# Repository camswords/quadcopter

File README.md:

The ThoughtWorks Sydney Quadcopter
==========

The ThoughtWorks Sydney Quadcopter is a quadcopter that is being built by the ThoughtWorks Sydney Community. 

To find out parts we have used, lessons we have learnt check out http://www.camswords.com/blog. To see photos of the quadcopter as it is built check out http://www.pinterest.com/camswords/the-thoughtworks-sydney-maker-day.

#### To disable Read Out Protection on new devices

1. Download the ST Link utility tool http://www.st.com/web/en/catalog/tools/PF258168

2. Install it on windows

3. Connect your ST Link USB device to your computer, and to your mini-m4

4. Try to connect, it will barf about not having permission. Set the Read Out Protection (under Option Bytes) to Level 0, no protection. 

5. Note that setting it to 2 will brick your mini-m4.

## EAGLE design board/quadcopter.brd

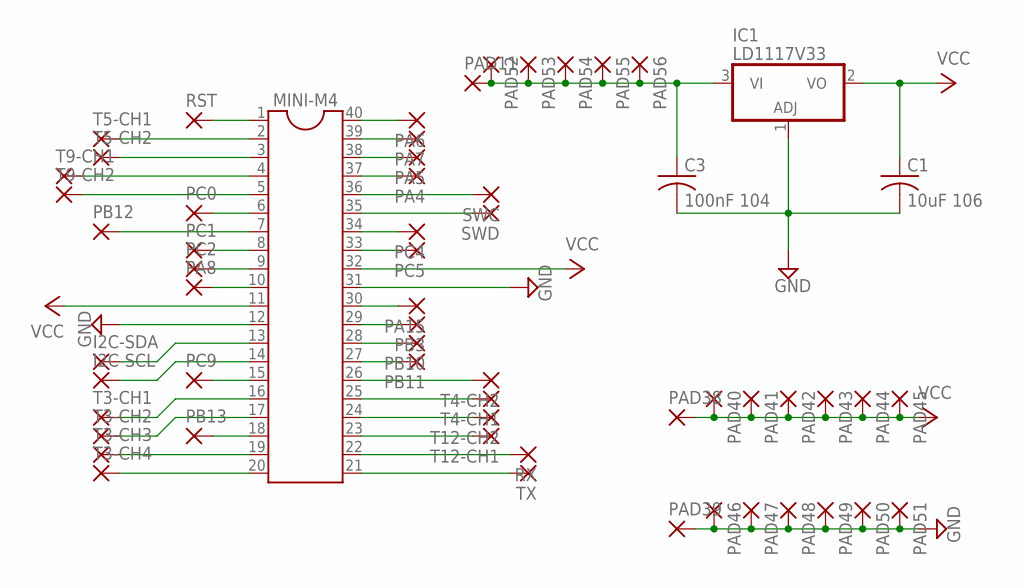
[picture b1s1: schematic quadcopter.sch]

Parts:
C1: 10uF 106; C025-040X050
C3: 100nF 104; C025-040X050
I2C-SCL, I2C-SDA: 1,6/0,8
IC1: LD1117V33; TO220H
MINI-M4: DIL40
PA4, PA5, PA6, PA7, PA8, PA15: 1,6/0,8
PAD11, PAD38, PAD39, PAD40, PAD41, PAD42, PAD43, PAD44, PAD45, PAD46, PAD47, PAD48, PAD49, PAD50, PAD51, PAD52, PAD53, PAD54, PAD55, PAD56: 1,6/0,8
PB3, PB10, PB11, PB12, PB13: 1,6/0,8
PC0, PC1, PC2, PC4, PC5, PC9: 1,6/0,8
RST: 1,6/0,8
RX: 1,6/0,8
SWC: 1,6/0,8
SWD: 1,6/0,8
T3-CH1, T3-CH2, T3-CH3, T3-CH4, T4-CH1, T4-CH2, T5-CH1, T5-CH2, T9-CH1, T9-CH2, T12-CH1, T12-CH2: 1,6/0,8
TX: 1,6/0,8

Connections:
GND: C1.2, C3.2, IC1.1 (ADJ), MINI-M4.12, MINI-M4.31, PAD39.1, PAD46.1, PAD47.1, PAD48.1, PAD49.1, PAD50.1, PAD51.1
unnamed: MINI-M4.2, T5-CH1.1
unnamed: MINI-M4.1, RST.1
unnamed: MINI-M4.3, T5-CH2.1
unnamed: MINI-M4.4, T9-CH1.1
unnamed: MINI-M4.6, PC0.1
unnamed: MINI-M4.5, T9-CH2.1
unnamed: MINI-M4.7, PB12.1
unnamed: MINI-M4.8, PC1.1
unnamed: MINI-M4.9, PC2.1
unnamed: MINI-M4.10, PA8.1
unnamed: MINI-M4.16, T3-CH1.1
unnamed: MINI-M4.17, T3-CH2.1
unnamed: I2C-SDA.1, MINI-M4.13
unnamed: I2C-SCL.1, MINI-M4.14
unnamed: C3.1, IC1.3 (VI), PAD11.1, PAD52.1, PAD53.1, PAD54.1, PAD55.1, PAD56.1
unnamed: MINI-M4.15, PC9.1
unnamed: MINI-M4.40, PA6.1
unnamed: MINI-M4.18, PB13.1
unnamed: MINI-M4.19, T3-CH3.1
unnamed: MINI-M4.20, T3-CH4.1
unnamed: MINI-M4.39, PA7.1
unnamed: MINI-M4.37, PA4.1
unnamed: MINI-M4.38, PA5.1
unnamed: MINI-M4.36, SWC.1
unnamed: MINI-M4.35, SWD.1
unnamed: MINI-M4.33, PC5.1
unnamed: MINI-M4.34, PC4.1
unnamed: MINI-M4.30, PA15.1
unnamed: MINI-M4.29, PB3.1
unnamed: MINI-M4.28, PB10.1
unnamed: MINI-M4.26, T4-CH2.1
unnamed: MINI-M4.27, PB11.1
unnamed: MINI-M4.25, T4-CH1.1
unnamed: MINI-M4.24, T12-CH2.1
unnamed: MINI-M4.22, RX.1
unnamed: MINI-M4.23, T12-CH1.1
unnamed: MINI-M4.21, TX.1
VCC: C1.1, IC1.2 (VO), MINI-M4.11, MINI-M4.32, PAD38.1, PAD40.1, PAD41.1, PAD42.1, PAD43.1, PAD44.1, PAD45.1

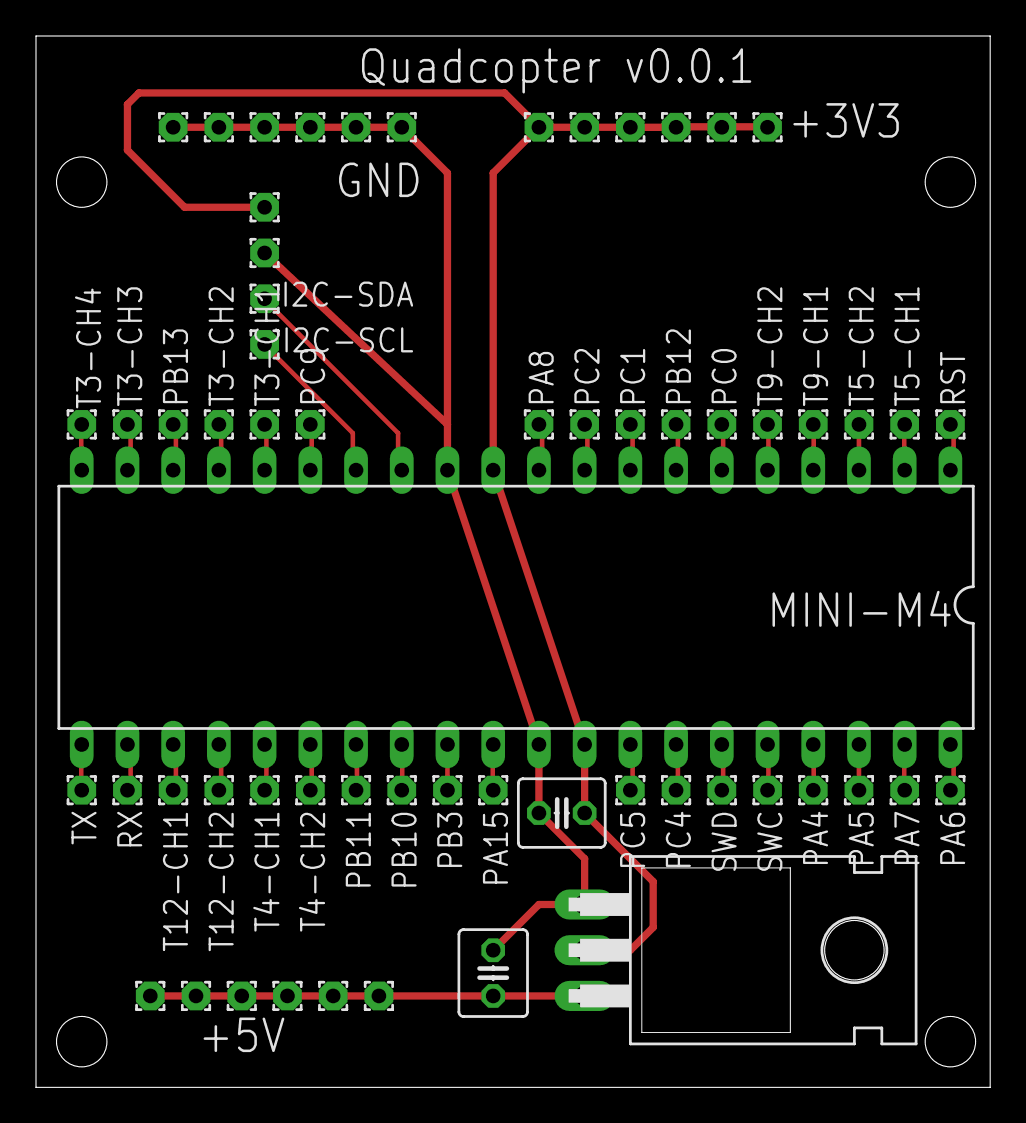
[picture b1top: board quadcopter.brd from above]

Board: 2 copper layers, 53.0 x 58.4 mm, 60 parts (0 on the bottom side), 39 nets.

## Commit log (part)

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2014-03-20 barfs when a file with streaming content is passed.
2014-03-20 fixed the test harness, added echo back in so that the code isnt passed to the test reporter
2014-04-03 sam/cam: added a simulator to understand more about pid controlling.
2014-04-06 added almond to the build so that all the code doesnt have to be written in one file
2014-04-06 moved the intensity stuff out to a module
2014-04-06 remove squire and almond from the project
2014-04-16 made the fake espruino path relative so that I dont have my username in the commit logs
2014-04-18 added a failing test that verifies whether the amd module overriding works or not
2014-04-18 converted the intensity tests to use the module loading
2014-04-19 move the it into its own module so that tests have less boilerplate
2014-04-20 added a spike of my initial thoughts of what the quad might look like
2014-04-20 moved the fail whale into the espruino namespace
2014-04-20 moved quad to quadcopter
2014-04-20 the spec helper does not require stubs to be specifed when there arent any
2014-04-20 the quadcopter uses the configuration for the throttle pin
2014-04-20 adding a watch will automatically calculate the duration
2014-04-20 the propeller can adjust throttles using a pwm output
2014-04-20 converted the boundaries of the propeller throttle to be between 1000 and 2000
2014-04-21 rename the setWatch module to be kebab case like the rest of the code
2014-04-21 converted the pid to be an amd module that can be deployed to the quad
2014-04-21 describe gotcha that Error does not exist
2014-04-26 added a random string generator, this will be used to define file names in analytics files.
2014-04-27 moved the fail whale to the utilities folder
2014-04-27 created an observer that will save the frequency that the quad loops over sensing and adjusting throttles
2014-04-27 moved watch to the utilities directory
2014-05-01 added espruino gotchas so that I don’t get caught out again.
2014-05-02 added a wiki to the project, it is too much too keep in one little brain!
2014-05-02 added APM as a potential for a flight controller
2014-05-03 separate the gulp file into multiple task files
2014-05-03 moved sensible defaults into the gulp espruino module, moved the espruino configuration for performance tests into the main gulpfile
2014-05-04 ensure the error object doesnt depend on fail whale, if there is a problem loading fail whale then we end up in a recursive loop until we stack overflow
2014-05-04 ensured the minify compression options are optimal for the espruino
2014-05-04 print a better error message when no espruino is connected and strategy is find first
2014-05-07 the scheduler can stop jobs
2014-05-08 killing the quadcopter will stop all scheduled jobs.
2014-05-08 removing functionality that is not used in the amd loader
2014-05-11 added some tests for a custom built promise library.
2014-05-11 added the beginnings of a new amd loader
2014-05-11 added a test to make sure define dependencies can be overridden
2014-05-12 clear the callbacks once a promise has been resolved, this reduces the memory footprint
2014-05-12 refactored the performance code into separate tasks
2014-05-14 testing the modules is now extracted out of the gulp file
2014-05-14 moved the deploy code out into a task separate from the gulpfile
2014-05-14 moved the paren to make it read better
2014-05-14 mangle the variable names so that they use less memory
2014-05-14 measure the memory being used for defining the Deferred class
2014-05-15 ensure that module deletion / optimisation does not occur during unit testing
2014-05-15 convert the record memory module option into a configuration parameter
2014-05-15 moved amd to the utility directory
2014-05-15 updated the ideas about what to do re memory
2014-05-17 added more dependencies to ensure that dependency names are returned of defined modules
2014-05-17 pass back an error message when attempting to omptimse amd modules with cyclic dependencies
2014-05-17 combine all of the ast module ordering into a module that can be used with gulp
2014-05-18 the application code is amd optimised before deploying to the espruino
2014-05-18 converted the performance running to use the optimised amd module loading
2014-05-19 print out the loop frequency during the performance tests
2014-06-01 ignore recordings that I make. any that are really important will still be committed, though in a different directory.
2014-06-04 convert set watch to disregard the event.lastTime, we dont trust it.
2014-06-09 saving analytics to file is a feature toggle as this probably wont be used.
2014-06-09 ensure the throttle is a number before saving it into the repository
2014-06-09 renamed the utility watch to be pwm specific
2014-06-09 simplify the scheduler by removing the named interval
2014-06-09 converted the loop frequency into a repository
2014-06-09 add the time to the sample analytics
2014-06-09 move the require for noble into the watch module exports function, this is because it was causing all of the gulp tasks to not finish
2014-06-09 record the output throttle, this hopefully should help determine why the motors intermittently turn off
2014-06-10 added info about installing the elua tools on a mac
2014-06-21 updating the wiki with a few more ideas
2014-06-23 the deploy script deleted the old build directory to ensure recompile every time; added a lua file that can trigger an interrupt.
2014-08-06 added the libraries and an initial make file that will build the bin file to be deployed to a stm32 microcontroller
2014-08-06 refactored the makefile to inline variables I dont think will ever change
2014-08-06 turn on all of the user driven leds on the stm32 discovery board
2014-08-06 the timer blinks a light every second
2014-08-07 lights turn on and off each second, though introduces heavy delays tying up the the cpu
2014-08-08 the timer runs at 50Hz and produces a 2ms high signal to represent a high throttle.
2014-08-08 use a systick timer to count seconds, turn lights on and off every second
2014-08-09 moved the systick configuration out into the systick file
2014-08-10 added note to make this code more efficient
2014-08-10 moved the timer to timer 3 to free up the led pins
2014-08-17 duty cycles can be set for each of the pwm channels
2014-08-18 removed the callbacks from systick, callbacks like this should be implemented using timers
2014-08-21 added a test harness to verify whether the pwm input is correct or not
2014-08-24 fire an interrupt when the counter counts up until the period
2014-08-25 made the pwm input flexible to abstract the timer, this will facilitate more inputs being added shortly.
2014-08-26 added resets in an attempt to avoid the deploy timeout problem
2014-08-26 throttle, rudder, airleron and elevator all can be captured at the same time.
2014-09-01 initialise the gyroscope using i2c
2014-09-04 read the registers one after the other, requires significantly less data to communicate the same message
2014-09-04 initialised the accelerometer
2014-09-04 when initialising PWM outputs, ensure they start at 0% not 100%
2014-09-07 calibrated the gyro on initialisation
2014-09-10 analytics are sent successfully via bluetooth
2014-09-10 the analytics successfully are printed to the screen for the loops per second
2014-09-15 removed analytics until they are useful
2014-09-15 attempting to use the gyroscope as a way of determining the angular position, so far it seems to be very unstable.
2014-09-15 the rfduino will only ever ask for one analytics value at a time
2014-09-15 round the floats before sending over the wire, send them as integers instead.
2014-09-15 increase the speed of the serial connection
2014-09-26 the pid calculates adjustments for the motor throttles
2014-09-27 added the ability to factor gyro drift into the angular position reading
2014-09-27 calibrate the gyro drift to ensure more accurate readings
2014-09-28 clean up the analytics output to be easier to read
2014-09-28 reset the angular position to zero every ten seconds to make it easier to debug
2014-10-01 added a faux calculated pulse, this is to make sure that small float values add up to something meaningful
2014-10-01 move the throttle to a neutral (50%) position, zero isn't helpful; ensure the analytics print out the right props on the right axis
2014-10-06 added grafana as a way to display what is happening to the quad
2014-10-06 added a js gulpfile so that I dont always have to require the coffeescript extension
2014-10-07 send statistics to the influxdb instead of writing them to the screen
2014-10-08 renamed the analytics folder to be server specific
2014-10-08 moved the persistence out of the analytics router
2014-10-08 remove the magnetometer code, it looks like it is sending to the wrong address
2014-10-08 Revert "ensure we only use the angular position when we can trust its value"
    This reverts commit ccca8ee1c8178dc9e3262ffe0e5f6883bd736434.
2014-10-08 reduce the number of attempts to get the i2c result, this drastically increases the loop frequency
2014-10-08 separate the serialisation from the gulp task for analytics
2014-10-11 ignore the mac ds store file
2014-10-11 create a buffer so that we can gradually send the analytics out via the xbees
2014-10-11 added a smoothing mechanism
2014-10-11 added the debug configuration to source control
2014-10-11 smooth the remote controls so that the angular position is not reset unless we press the button on the handset
2014-10-12 ignore the workspace.xml file as it changes too often
2014-10-12 use the gyro at the lowest bandwidth low pass filter, it should amount to less noise
2014-10-12 convert the analytics to push fewer characters more frequently, it seems to have a smaller error rate.
2014-10-14 remove the drift offset, this should be instead done using a low pass filter.
2014-10-14 add some notes for tomorrow night when I try to fly
2014-11-02 comment out the remote controls until I can get a taranis that is working
2014-11-26 remove smarts that were keeping the duty cycle and frequency pegged to the same value
2014-12-12 remove the throttle input while testing, add the xbee profiles to source control
2014-12-13 apply the gyro offset after the raw value has been converted to degrees per second
2014-12-14 enable clock stretching to give peripherals a chance to catchup if things are moving too fast
2014-12-14 the accelerometer works using interrupts :-)
2014-12-14 the gyroscope uses the same interrupt mechanism to get the values from the i2c bus
2014-12-15 make the accelerometer align with the positive / negative gyroscope x axis; only this way can they be combined together in a complimentary filter
2014-12-17 separate configuration into defines in one file
2014-12-28 replace the analytics with mavlink
2015-01-07 revert the mavlink changes. The mavlink clients didn't seem very useful and I found it hard to send all of the messages that I wanted.
2015-01-10 the analytics router understands the basics of the new metrics protocol
2015-01-10 save the analytics to the influx database so they can be displayed on a graph
2015-01-10 fixed defect where the time was being incorrectly calculated
2015-01-10 accidentally reverted the fix to 100% throttle, so putting it back
2015-01-10 cleaning up the pwm input signals means that I should no longer need input smoothing
2015-01-11 moving the front of the quad up in an x or y direction corresponds to a positive increase along the x or y axis
2015-01-17 changed the way that we interpret throttle so that the quad will hover by default
2015-01-17 reduced the pid proportional and motor speed to take off to assist in tuning
2015-01-24 created a task to generate random noise
2015-03-11 updated the board layout and routed the voltage regulator
